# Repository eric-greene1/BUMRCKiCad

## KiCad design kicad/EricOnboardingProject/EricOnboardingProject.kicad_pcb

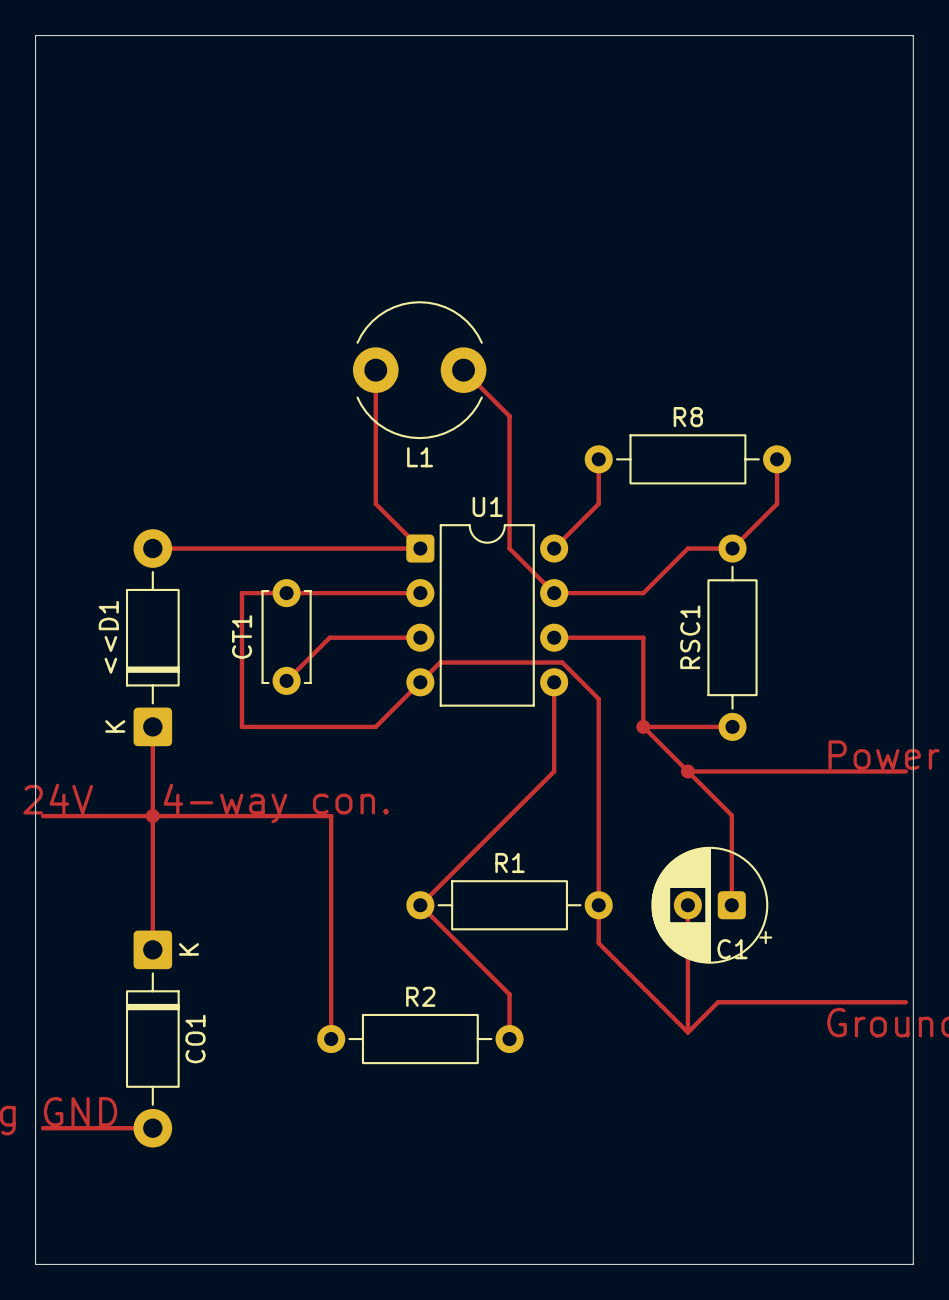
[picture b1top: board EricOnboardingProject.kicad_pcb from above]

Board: 4 copper layers, 50.0 x 70.0 mm, 10 parts (0 on the bottom side), 8 nets.

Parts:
<<D1: 1N5819; D_DO-41_SOD81_P10.16mm_Horizontal
C1: 100μf; CP_Radial_D6.3mm_P2.50mm
CO1: 330μf; D_DO-41_SOD81_P10.16mm_Horizontal
CT1: 680pf; C_Disc_D5.0mm_W2.5mm_P5.00mm
L1: 220 uH; L_Radial_D7.5mm_P5.00mm_Fastron_07P
R1: 100+10+10Ω; R_Axial_DIN0207_L6.3mm_D2.5mm_P10.16mm_Horizontal
R2: 2200Ω; R_Axial_DIN0207_L6.3mm_D2.5mm_P10.16mm_Horizontal
R8: 180Ω; R_Axial_DIN0207_L6.3mm_D2.5mm_P10.16mm_Horizontal
RSC1: .22Ω; R_Axial_DIN0207_L6.3mm_D2.5mm_P10.16mm_Horizontal
U1: MC34063AP; DIP-8_W7.62mm

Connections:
GND: C1.2, CT1.2, R1.2, U1.2 (SwE), U1.4 (GND)
unnamed: <<D1.2 (A), L1.2, U1.1 (SwC)
unnamed: <<D1.1 (K), CO1.1, R2.1
unnamed: R8.1, U1.8 (DC)
unnamed: L1.1, R8.2, RSC1.2, U1.7 (Ipk)
unnamed: CT1.1, U1.3 (TC)
unnamed: R1.1, R2.2, U1.5 (Vfb)
unnamed: C1.1, RSC1.1, U1.6 (Vin)
